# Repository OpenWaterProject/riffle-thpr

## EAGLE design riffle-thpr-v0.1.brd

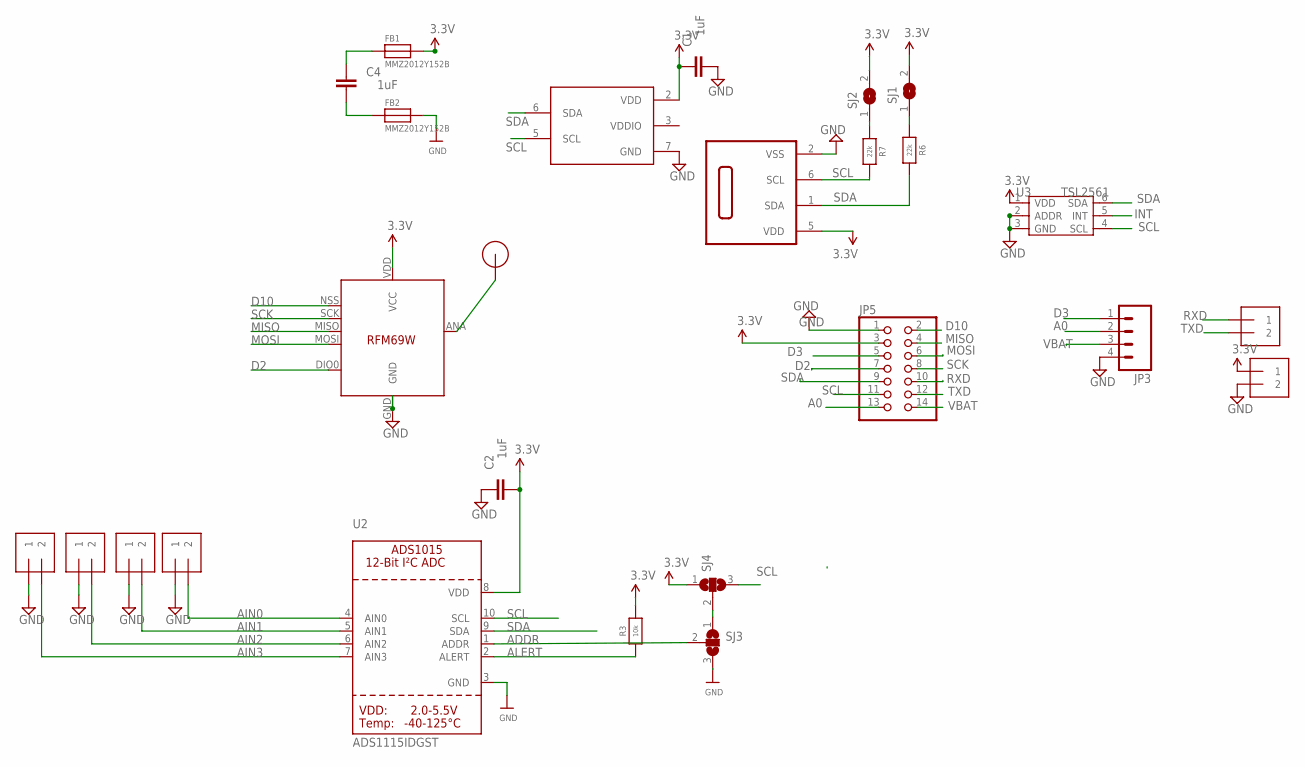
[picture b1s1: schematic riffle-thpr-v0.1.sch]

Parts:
C1, C2, C4: 1uF; 0603-CAP
FB1, FB2: MMZ2012Y152B; 0805
IN0, IN1, IN2, IN3, IN4, IN5: 1X2-3.5MM
JP3: M04SMD; 1X04-SMD
JP5: PINHD-2X7; 2X07
R3: 10k; 0603-NO
R6, R7: 22k; 0603-NO
SJ1, SJ2: SJ
SJ3, SJ4: SJ2W; SJ_2
SN1: SHT21; DFN6/SHT
U1: BMP180
U2: ADS1115IDGST; MSOP10
U3: TSL2561; TMB-6
U$1: RFM12B_ANTENNA; RFM12B-ANTENNA
U$5: RFM69; RFM69W-MINPADS

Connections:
A0: JP3.2, JP5.13
ADDR: SJ3.2, U2.1 (ADDR)
AIN0: IN0.2, U2.4 (AIN0)
AIN1: IN1.2, U2.5 (AIN1)
AIN2: IN2.2, U2.6 (AIN2)
AIN3: IN3.2, U2.7 (AIN3)
ALERT: R3.1, U2.2 (ALERT)
D2: JP5.7, U$5.DIO0
D3: JP3.1, JP5.5
D10: JP5.2, U$5.NSS (SEL)
GND: C1.1, C2.2, FB2.2, IN0.1, IN1.1, IN2.1, IN3.1, IN5.2, JP3.4, JP5.1, SJ3.3, SN1.2 (VSS), U1.7 (GND), U2.3 (GND), U3.2 (ADDR), U3.3 (GND), U$5.GND
INT: U3.5 (INT)
MISO: JP5.4, U$5.MISO
MOSI: JP5.6, U$5.MOSI
unnamed: C4.2, FB1.1
unnamed: C4.1, FB2.1
unnamed: SJ3.1, SJ4.2
unnamed: R6.1, SJ1.1
unnamed: R7.1, SJ2.1
unnamed: U$1.P$1, U$5.ANA (ANT)
RXD: IN4.1, JP5.10
SCK: JP5.8, U$5.SCK
SCL: JP5.11, R7.2, SJ4.3, SN1.6 (SCL), U1.5 (SCL), U2.10 (SCL), U3.4 (SCL)
SDA: JP5.9, R6.2, SN1.1 (SDA), U1.6 (SDA), U2.9 (SDA), U3.6 (SDA)
TXD: IN4.2, JP5.12
VBAT: JP3.3, JP5.14
VCC: C1.2, C2.1, FB1.2, IN5.1, JP5.3, R3.2, SJ1.2, SJ2.2, SJ4.1, SN1.5 (VDD), U1.2 (VDD), U2.8 (VDD), U3.1 (VDD), U$5.VDD (VCC)
VDDIO: U1.3 (VDDIO)

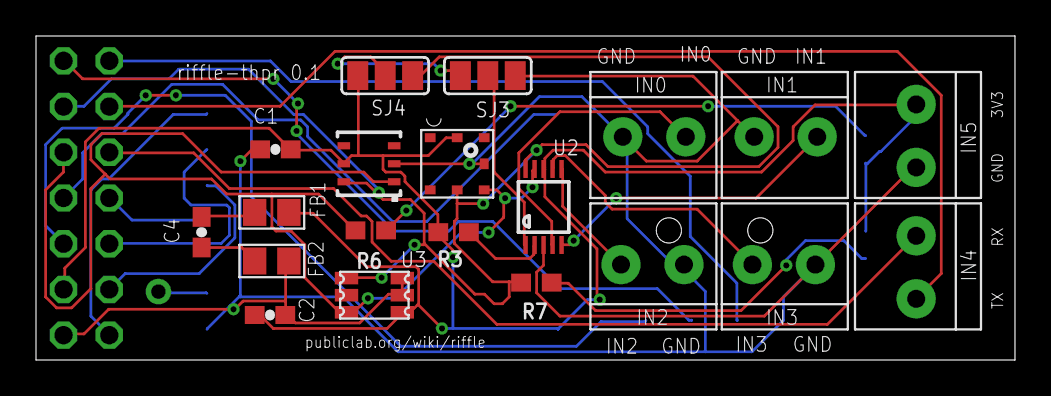
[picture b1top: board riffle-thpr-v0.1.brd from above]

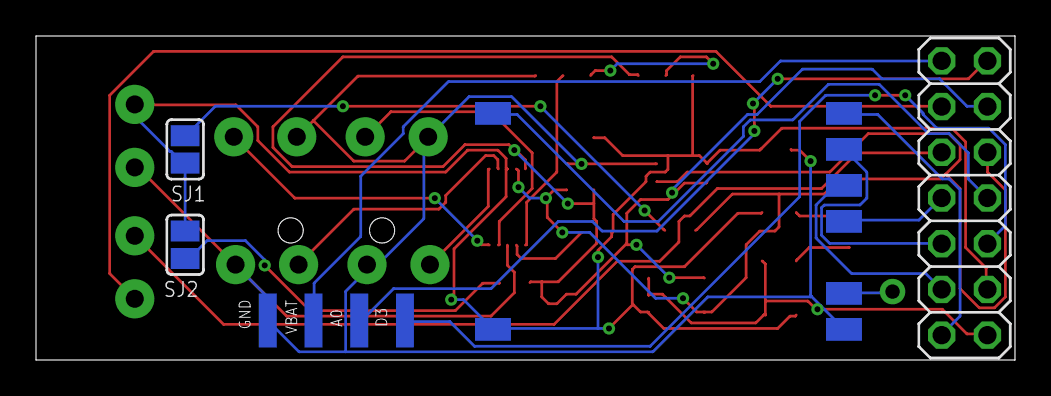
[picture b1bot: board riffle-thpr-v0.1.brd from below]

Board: 2 copper layers, 54.4 x 18.0 mm, 26 parts (5 on the bottom side), 26 nets.

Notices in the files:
parts and their libraries:
microbuilder: This work is placed in the public domain, and may be freely used for commercial and non-commercial work with the following conditions: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
